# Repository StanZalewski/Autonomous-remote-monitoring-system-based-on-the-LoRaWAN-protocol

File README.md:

# Autonomous Remote Monitoring System (LoRaWAN)

Solar-powered agricultural weather station built from scratch: three custom PCBs, three MCUs, Modbus RTU over RS-485 between boards, LoRaWAN uplink to a private ChirpStack network server. Verified 4.3 km link in suburban terrain.

Bachelor's thesis project, Poznan University of Technology, 2026.

---

## What it does

A field station measures temperature, humidity, pressure and ambient light, runs entirely off a 30 W solar panel with a 3S LiFePO4 pack, and reports over LoRaWAN to a self-hosted network server. No GSM, no mains power, no cloud dependency.

| | |
|---|---|
| **Boards designed** | 3 (two 4-layer, one 2-layer), schematic → routing → assembly → bring-up |
| **Bare-metal drivers written** | 5, from IC datasheets: BMP390, SHT45, VEML7700, BQ25798, BQ76952 |
| **Verified LoRa range** | 4.3 km, suburban terrain, low-mounted gateway |
| **Inter-board protocol** | Modbus RTU over RS-485, master–slave, expandable to 32 nodes |
| **MCUs** | STM32WLE5CC (RAK3172 master), 2× STM32G030F6 (slaves) |

---

## System architecture

```mermaid
flowchart LR
  ED["End device<br/>3 PCBs, Modbus RTU"] -->|"LoRa 868 MHz"| GW["RAK5146 gateway<br/>ChirpStack Gateway OS"]
  GW -->|Ethernet| LNS["ChirpStack v4<br/>network server"]
  LNS -->|MQTT| BR["Mosquitto broker"]
  BR --> DB[("InfluxDB<br/>time-series")]
  BR --> WEB["Web interface"]
  DB --> WEB
```

### End device

```mermaid
flowchart TB
  M["<b>Master</b><br/>RAK3172 (STM32WLE5CC)<br/>LoRaWAN + GPS"]
  P["<b>Power board</b><br/>BQ25798 MPPT charger<br/>BQ76952 BMS<br/>STM32G030F6"]
  S["<b>Sensor board</b><br/>SHT45 · BMP390 · VEML7700<br/>STM32G030F6"]
  M ---|"RS-485 bus"| P
  M ---|"RS-485 bus"| S
```

The split into three boards is deliberate: each module is reusable on its own, and new slaves can be added to the bus without touching the existing hardware.

---

## Hardware

### Wireless transceiver — master (4-layer)

RAK3172 (STM32WLE5CC) running the LoRaWAN stack and mastering the Modbus bus, plus a Quectel LC76GABMD GNSS receiver. USB-C to UART via FT234XD behind an STISO621 optoisolator for bench work, SP3485EN for the RS-485 side, TLV75533 LDO.

| Top | Bottom | Assembled |
|---|---|---|
|  |  |  |

Both antennas are fed by 50 Ω controlled-impedance traces — 0.3493 mm width computed for the JLCPCB FR-4 stackup, with a pi network at each antenna for fine tuning. The GNSS feed runs up the centre of the board inside a via fence, with the SMD antenna (E1) at the top edge and the whole area kept clear of copper on the layer below. The RAK3172 sits in the opposite corner with its own SMA feed, so the two RF chains never share a return path. Power electronics and high-current traces are pushed as far from both as the outline allows.

Schematics: [RAK3172 and peripherals](docs/schematics/transceiver-rak3172.svg) · [GNSS section](docs/schematics/transceiver-gps.svg)

### Power electronics — slave (4-layer)

BQ25798 buck-boost charger with MPPT harvesting from a 30 W panel into a 3S LiFePO4 pack, BQ76952 BMS, STM32G030F6 supervising both over a galvanically isolated I²C bus.

| Top | Bottom | Assembled |
|---|---|---|
|  |  |  |

Two constraints drove this layout: minimise EMI, minimise high-current path length. The 2.2 µH inductor sits at the top (750 kHz switching was chosen over the 1 µH / 1.5 MHz option for better efficiency and lower EMI), decoupling caps are pulled tight to the charger's VBUS, SYS, PMID and BAT pins, and the analog and power grounds are split and joined at a single point between C10 and C11. The BMS and its circuitry are placed physically between the MCU and the charger as a buffer against the switching node. The charge and discharge FETs sit top-right of the BMS to keep pack current paths short, and the 1 mΩ shunt (R23) divides BMS ground from system ground. Everything crossing to the MCU passes through ISO1640 (I²C) and Si8662 (ALERT, INT, CE) isolators, fed by isolated 5 V and 12 V DC-DC bricks.

Schematics: [BQ25798 charger](docs/schematics/power-charger-bq25798.svg) · [BQ76952 BMS](docs/schematics/power-bms-bq76952.svg) · [MCU and isolation](docs/schematics/power-mcu-g030f6.svg)

### Data gathering — slave (2-layer)

SHT45 (±0.1 °C, ±1 %RH), BMP390 (±0.33 hPa) and VEML7700 on one I²C bus, read by an STM32G030F6 and exposed as Modbus registers. Spare GPIO is broken out to terminal blocks for wind and rain sensors.

| Top | Bottom | Assembled |
|---|---|---|
|  |  |  |

The VEML7700 is mounted alone on the back face; everything else lives on the front. That keeps direct sun off the SHT45, which would otherwise bias the temperature reading, and leaves the light sensor as the only protrusion on its side so the enclosure aperture can stay small. The bottom face is a solid ground pour for a continuous low-impedance return, and the LDO sits next to the terminal blocks to keep the long, EMI-prone wiring runs away from the sensor traces.

Schematic: [sensor board](docs/schematics/sensor-board.svg)

---

## Firmware

Written bare-metal against the datasheets on a CMake / `arm-none-eabi` toolchain, not inside an IDE. Each module follows the same three-way split:

```
<Module>/
├── App/          # init, control, RS-485 dock — application logic
├── Core/         # CubeMX-generated, with calls into App/
├── Drivers_IC/   # or Drivers_Sensors/ — direct IC control
└── Drivers_ModbusRTU/
```

Keeping everything outside `Core/` means CubeMX regeneration never touches hand-written code, and the drivers port to another MCU without untangling them first.

### Power module sequence

```mermaid
flowchart TB
  A["fullInitialization()<br/>health check → configure → verify<br/>→ open CHG/DSG FETs → enable charging"]
  B["RS485_Init()<br/>RE/DE low, UART RX interrupt"]
  C["GenSysInfo()<br/>cell voltages, pack temps, FET state"]
  D["RS485_UpdateRegisters()"]
  E["RS485_Process()<br/>handle master requests"]
  F["every 60 s:<br/>WatchDogs_R() → HealthCheck() → UpdateFlags()"]
  A --> B --> C --> D --> E --> C
  E -.-> F
  F -.-> C
```

The board only comes up if the charger's VBUS is live: with the BMS FETs open, the isolated side has no power and I²C would fail, so the charger's default battery profile bootstraps the DC-DC that feeds the MCU. Initialisation then health-checks both ICs (device ID on the bus, no fault flags raised), configures them, verifies the critical registers read back correctly, and only then opens the CHG and DSG FETs so the charger sees the pack on its BAT pin.

Both ICs run hardware watchdogs with an 80 s timeout; the loop kicks them every 60 s and re-runs the same health check used at boot. Fault and status registers are mirrored into Modbus registers, so a fault on the power board propagates to the master and out over LoRa rather than silently bricking the station.

### LoRa payload

Uplinks are packed hexadecimal, not JSON — air time matters under the EU 1% duty cycle. Each payload opens with a two-byte identifier (payload class + device ID matching the Modbus address). Values are sent unscaled big-endian `uint16_t`, with signed quantities cast from `int16_t`; pressure and lux use `uint32_t`. Example: a cell voltage of 3.456 V goes out as `3456` → `0x0D80`.

| Payload ID | Contents |
|---|---|
| `0x01` | Cell voltages 1–3, pack temperature (BMS side, charger side) |
| `0x11` | VAC_1 voltage, system info, BMS current |
| `0x21`–`0x81` | Fault checks, fault flags, charger flags, BMS safety alerts/status, PF alert/status |
| `0x02` | SHT45 temperature, SHT45 humidity, BMP390 temperature |
| `0x12` | VEML7700 lux, white ratio, BMP390 pressure |

Because sensor data is split across payload classes, the decoder keeps a per-station cache and merges partial updates into a complete record.

---

## Network side

A private LoRaWAN deployment rather than The Things Network — too few public gateways in the test area, and no control over their uptime. ChirpStack v4 runs in Docker Compose on an Odroid H4; the gateway is a Raspberry Pi with a RAK5146 concentrator HAT running ChirpStack Gateway OS, feeding an 80 cm outdoor fiberglass omni.

---

## Results and what didn't work

Worth reading before the achievements list. Three limitations showed up only in the field:

**DC-DC efficiency at low load.** The converter draws more quiescent current than budgeted, so after roughly 10 hours without sun the station drops out and stays down until the panel recovers. Fine for summer, not good enough for a Polish winter. A lower-Iq regulator and a proper sleep state for the master are the fix.

**LiFePO4 below freezing.** The cells cannot be charged below 0 °C without permanent damage, and this wasn't caught at design time. Sub-zero temperatures are normal here in winter, so a heater circuit and a charge inhibit tied to the BMS thermistor are required for year-round autonomy.

**GPS never acquires a fix.** The LC76GABMD powers up and outputs data over UART, but no satellites are found even after 30 minutes with a clear sky view. Most likely the passive SMD antenna placement and matching — the next revision needs the ground-plane keepout and feed geometry reworked against the Quectel application note, and an active antenna as a fallback.

What did work: Modbus RTU between modules ran without a single bus fault across deployment, the LoRaWAN join succeeded at 4.3 km despite a gateway mounted low with terrain intruding into the Fresnel zone, and the charger/BMS pair managed the solar-to-battery handover autonomously.

---

## In progress: anemometer

The sensor board breaks out spare GPIO to terminal blocks specifically so wind and rain sensors can be added without a redesign. The anemometer is the first of them — mechanically designed, board routed, not yet built.

| Cross-section | Sensor PCB |
|---|---|
|  |  |

Three-cup rotor on a vertical shaft running in two stacked bearings, with the rotating magnet passing directly over a Hall sensor on a round PCB at the base of the housing. The board is the smallest one in the project: a 5 V to 3.3 V regulator (U3) with its decoupling, the Hall sensor (U1), a pull-up on its open-drain output (R1), and three pads — 5 V, GND, OUT. Output is a pulse train straight into one of the sensor board's binary inputs, so wind speed becomes a frequency count rather than another I²C device on the bus.

The board outline wraps the shaft bore, and the signal trace is routed the long way around the perimeter rather than across the centre, keeping it clear of the bore and the mounting holes. The housing overhangs the whole assembly so the bearings and electronics sit under a drip edge.

Not yet fabricated — the mechanical design is done, the electrical design is done, and the build was cut for time.

---

## Build

```bash
cmake -B build -DCMAKE_TOOLCHAIN_FILE=cmake/arm-none-eabi.cmake
cmake --build build
```

Flash with `st-flash` or an ST-Link through OpenOCD. The RAK3172 is configured through RUI3 APIs; the two STM32G030F6 slaves are flashed over SWD on the KAmod BlackPico headers.

---

## Repository layout

```
PowerManagementModule/     # STM32G030F6 — charger, BMS, Modbus slave
DataGatheringModule/       # STM32G030F6 — sensors, Modbus slave
TransceiverModule/         # RAK3172 — Modbus master, LoRaWAN uplink
hardware/                  # KiCad projects, Gerbers, BOMs
docs/img/                  # board renders and photos
docs/schematics/           # exported schematic sheets
```

---

## Authorship

Joint bachelor's thesis with **Jakub Wesołowski**, supervised by dr inż. Bartłomiej Wicher.

This repository covers the end device. My contribution: hardware design and PCB layout of all three boards, all embedded firmware and IC drivers, the Modbus RTU / RS-485 transport, the LoRa payload protocol, and the end-device integration with the ChirpStack network server (thesis sections 2 and 3.2–3.6).

The application layer — MQTT broker, InfluxDB schema, web interface and the Gradient Boosting prediction model (sections 3.1, 3.7 and chapter 4) — is Jakub's work.

---

## License

MIT for the firmware. Hardware files under CERN-OHL-P v2.

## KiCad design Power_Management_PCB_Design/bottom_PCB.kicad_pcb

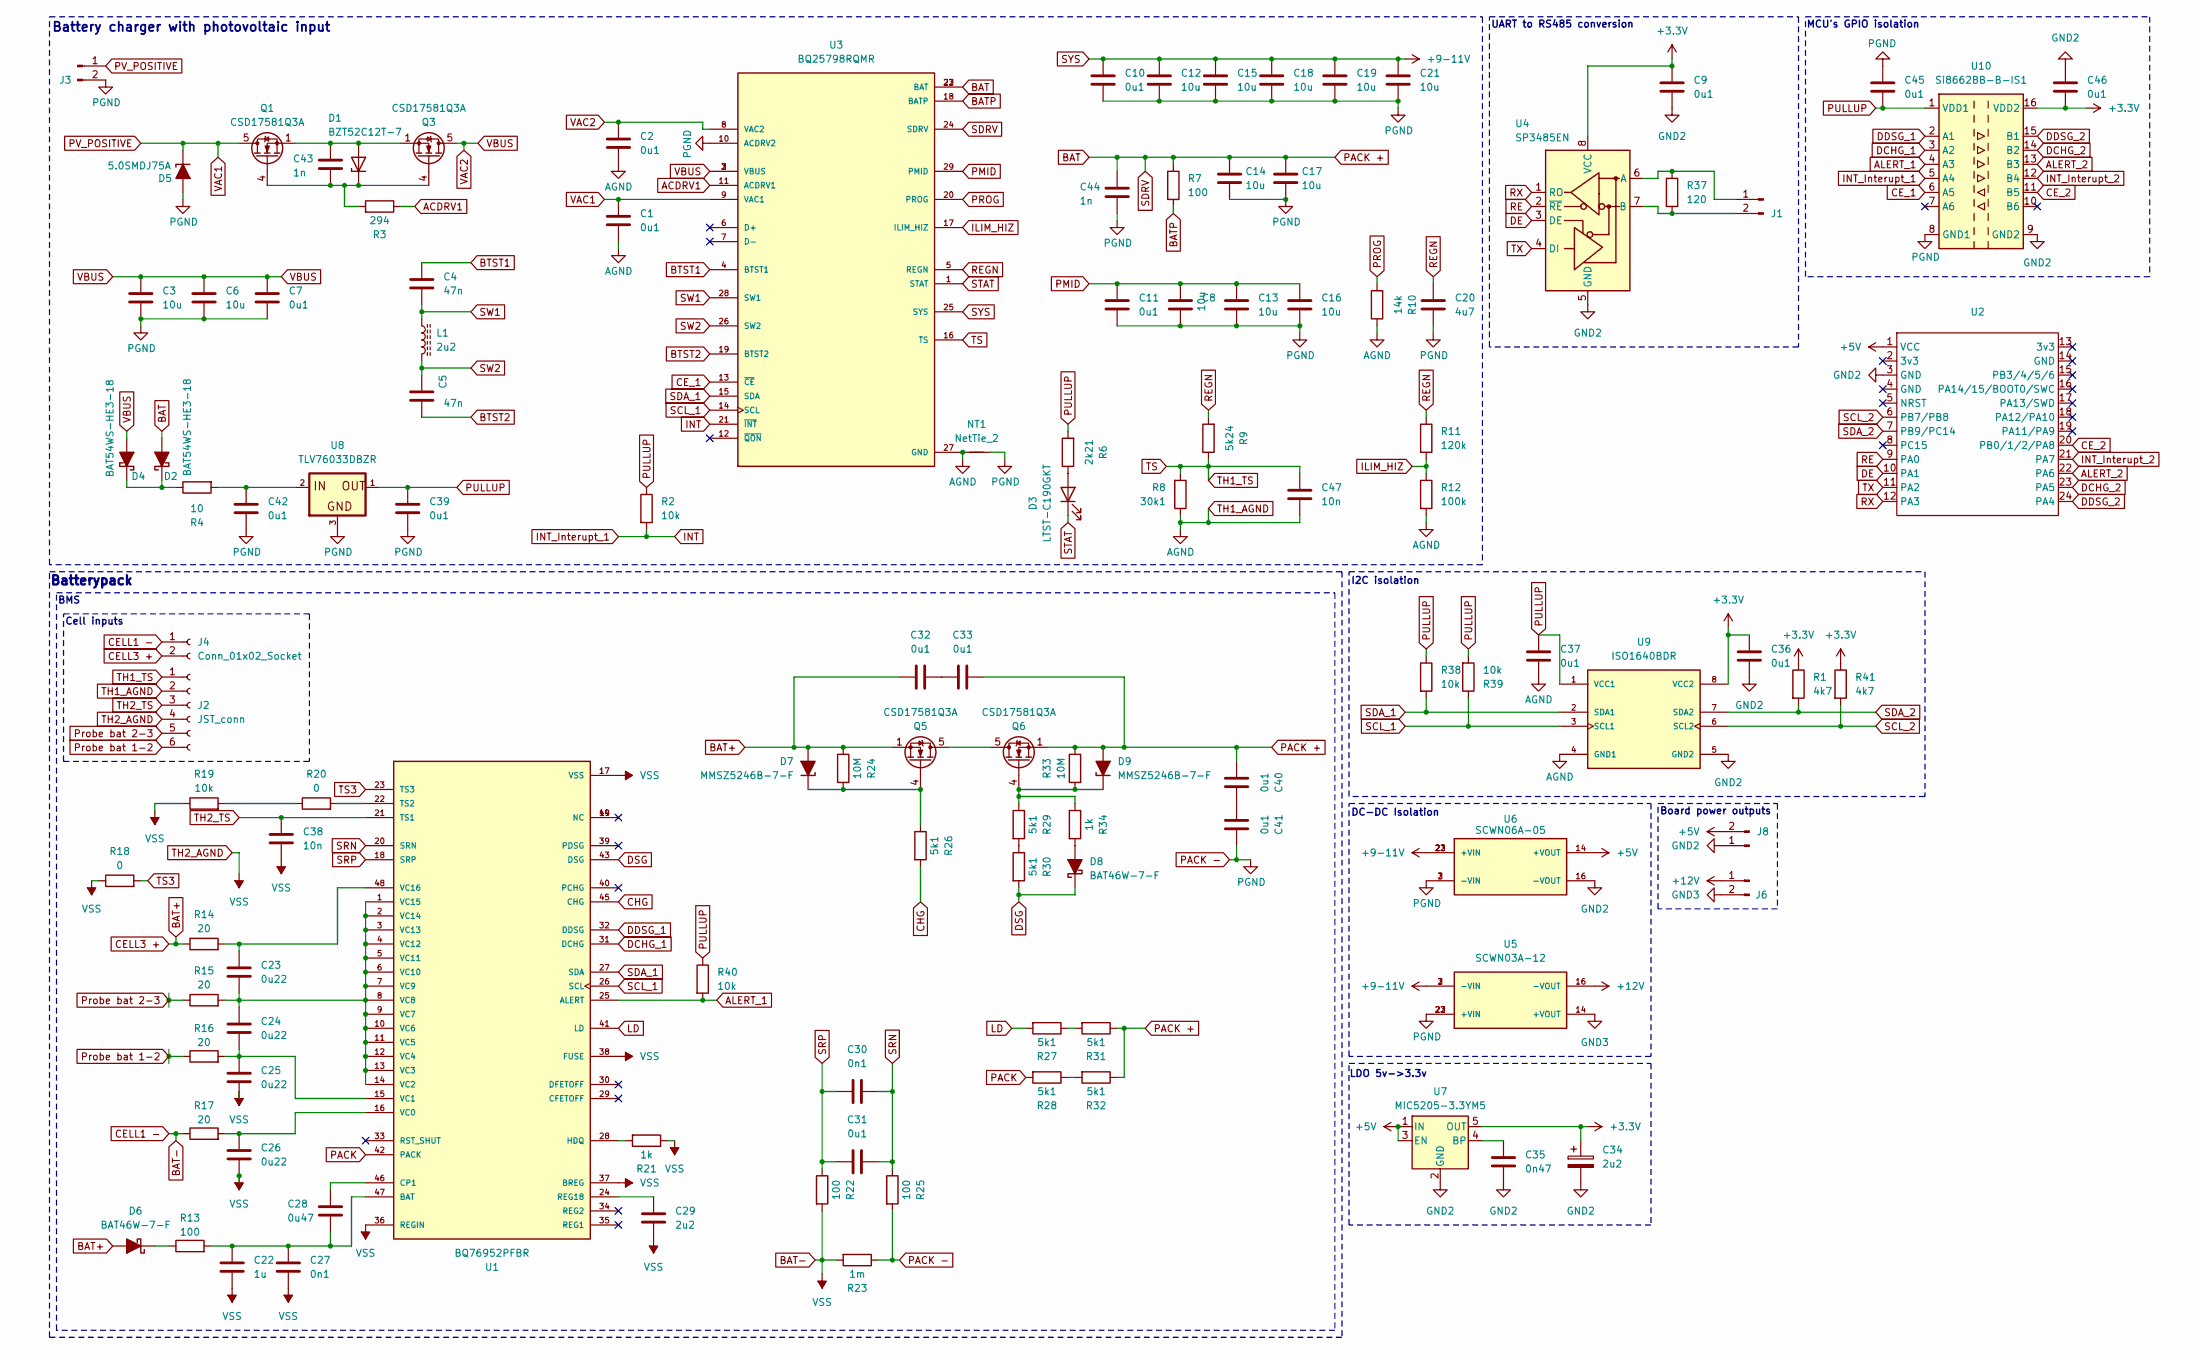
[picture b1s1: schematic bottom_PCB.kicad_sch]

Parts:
C1, C2, C7, C9, C10, C11, C31, C32, C33, C36, C37, C39, C40, C41, C42, C45, C46: 0u1; C_0603_1608Metric_Pad1.08x0.95mm_HandSolder
C3, C6, C8, C12, C13, C15, C16, C18, C19, C21: 10u; C_1206_3216Metric_Pad1.33x1.80mm_HandSolder
C4, C5: 47n; C_0603_1608Metric_Pad1.08x0.95mm_HandSolder
C14, C17: 10u; C_0603_1608Metric_Pad1.08x0.95mm_HandSolder
C20: 4u7; C_0603_1608Metric_Pad1.08x0.95mm_HandSolder
C22: 1u; C_1206_3216Metric_Pad1.33x1.80mm_HandSolder
C23, C24, C25, C26: 0u22; C_0603_1608Metric_Pad1.08x0.95mm_HandSolder
C27, C30: 0n1; C_0603_1608Metric_Pad1.08x0.95mm_HandSolder
C28: 0u47; C_0805_2012Metric_Pad1.18x1.45mm_HandSolder
C29: 2u2; C_0805_2012Metric_Pad1.18x1.45mm_HandSolder
C34: 2u2; C_1206_3216Metric_Pad1.33x1.80mm_HandSolder
C35: 0n47; C_0603_1608Metric_Pad1.08x0.95mm_HandSolder
C38, C47: 10n; C_0805_2012Metric_Pad1.18x1.45mm_HandSolder
C43, C44: 1n; C_0603_1608Metric_Pad1.08x0.95mm_HandSolder
D1: BZT52C12T-7; D_SOD-523
D2, D4: BAT54WS-HE3-18; D_SOD-323_HandSoldering
D3: LTST-C190GKT; LED_0603_1608Metric_Pad1.05x0.95mm_HandSolder
D5: 5.0SMDJ75A; DIOM6859X262N
D6, D8: BAT46W-7-F; D_SOD-123
D7, D9: MMSZ5246B-7-F; D_SOD-123
J1, J6, J8: Conn_01x02_Pin; SPTAF 1_2-3,5-IL
J2: JST_conn; JST_PH_B6B-PH-K_1x06_P2.00mm_Vertical
J3: Conn_01x02_Pin; conn_SMD_wire_2x1_Power
J4: Conn_01x02_Socket; AMASS_XT60-M_1x02_P7.20mm_Vertical
L1: 2u2; SPM6530T-2R2M
NT1: NetTie_2; NetTie
Q1, Q3, Q5, Q6: CSD17581Q3A; VSON-8_3.3x3.3mm_P0.65mm_NexFET
R1, R41: 4k7; R_0603_1608Metric_Pad0.98x0.95mm_HandSolder
R2, R38, R39, R40: 10k; R_0603_1608Metric_Pad0.98x0.95mm_HandSolder
R3: 294; R_0603_1608Metric_Pad0.98x0.95mm_HandSolder
R4: 10; R_1206_3216Metric_Pad1.30x1.75mm_HandSolder
R6: 2k21; R_0603_1608Metric_Pad0.98x0.95mm_HandSolder
R7, R13, R22, R25: 100; R_0603_1608Metric_Pad0.98x0.95mm_HandSolder
R8: 30k1; R_0603_1608Metric_Pad0.98x0.95mm_HandSolder
R9: 5k24; R_0603_1608Metric_Pad0.98x0.95mm_HandSolder
R10: 14k; R_0603_1608Metric_Pad0.98x0.95mm_HandSolder
R11: 120k; R_0603_1608Metric_Pad0.98x0.95mm_HandSolder
R12: 100k; R_0603_1608Metric_Pad0.98x0.95mm_HandSolder
R14, R15, R16, R17: 20; R_0805_2012Metric_Pad1.20x1.40mm_HandSolder
R18, R20: 0; R_0603_1608Metric_Pad0.98x0.95mm_HandSolder
R19: 10k; R_1206_3216Metric_Pad1.30x1.75mm_HandSolder
R21: 1k; R_0603_1608Metric
R23: 1m; R_1210_3225Metric_Pad1.30x2.65mm_HandSolder
R24, R33: 10M; R_0603_1608Metric_Pad0.98x0.95mm_HandSolder
R26, R27, R28, R29, R30, R31, R32: 5k1; R_0805_2012Metric_Pad1.20x1.40mm_HandSolder
R34: 1k; R_0805_2012Metric_Pad1.20x1.40mm_HandSolder
R37: 120; R_0603_1608Metric_Pad0.98x0.95mm_HandSolder
U1: BQ76952PFBR; TQFP-48_7x7mm_P0.5mm; PARTREV B
U2: STM32G030
U3: BQ25798RQMR; IC_BQ25798RQMR; PARTREV B
U4: SP3485EN; SOIC-8_3.9x4.9mm_P1.27mm
U5: SCWN03A-12; DIP1524W50P254L3180H1020Q8B; PARTREV N/A
U6: SCWN06A-05; DIP1524W50P254L3180H1020Q8B; PARTREV N/A
U7: MIC5205-3.3YM5; SOT-23-5
U8: TLV76033DBZR; SOT-23-3
U9: ISO1640BDR; SOIC127P599X175-8N; PARTREV D
U10: Si8662BB-B-IS1; SOIC-16_3.9x9.9mm_P1.27mm

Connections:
+3.3V: C9.1, C34.1, C36.1, C46.2, R1.1, R41.1, U4.8 (VCC), U7.5 (OUT), U9.8 (VCC2), U10.16 (VDD2)
+5V: J8.2, U2.1 (VCC), U6.14 (+VOUT), U7.1 (IN), U7.3 (EN)
+12V: J6.1, U5.16 (-VOUT)
ACDRV1: R3.1, U3.11 (ACDRV1)
ALERT_1: R40.2, U1.25 (ALERT), U10.4 (A3)
ALERT_2: U2.22 (PA6), U10.13 (B3)
BAT: C14.1, C17.1, C33.2, C40.1, C44.1, D2.2 (A), D9.2 (A), Q6.1 (S), Q6.2 (S), Q6.3 (S), R7.1, R31.1, R32.1, R33.1, U3.22 (BAT), U3.23 (BAT), U3.24 (SDRV)
BAT+: C32.1, D6.2 (A), D7.2 (A), J4.2, Q5.1 (S), Q5.2 (S), Q5.3 (S), R14.1, R24.1
BAT-: C22.2, C25.2, C26.2, C27.2, C29.2, C38.2, J2.4, J4.1, R17.1, R18.1, R19.1, R21.1, R22.2, R23.2, U1.17 (VSS), U1.36 (REGIN), U1.37 (BREG), U1.38 (FUSE)
BATP: R7.2, U3.18 (BATP)
BTST1: C4.1, U3.4 (BTST1)
BTST2: C5.2, U3.19 (BTST2)
CE_1: U3.13 (~CE), U10.6 (A5)
CE_2: U2.20 (PB0/1/2/PA8), U10.11 (B5)
CHG: R26.2, U1.45 (CHG)
DCHG_1: U1.31 (DCHG), U10.3 (A2)
DCHG_2: U2.23 (PA5), U10.14 (B2)
DDSG_1: U1.32 (DDSG), U10.2 (A1)
DDSG_2: U2.24 (PA4), U10.15 (B1)
DE: U2.10 (PA1), U4.3 (DE)
DSG: D8.1 (K), R30.2, U1.43 (DSG)
GND2: C9.2, C34.2, C35.2, C36.2, C46.1, J8.1, U2.3 (GND), U4.5 (GND), U6.16 (-VOUT), U7.2 (GND), U9.5 (GND2), U10.9 (GND2)
GND3: J6.2, U5.14 (+VOUT)
ILIM_HIZ: R11.2, R12.1, U3.17 (ILIM_HIZ)
INT: R2.2, U3.21 (~INT), U10.5 (A4)
INT_Interupt_2: U2.21 (PA7), U10.12 (B4)
LD: R27.2, U1.41 (LD)
unnamed: C32.2, C33.1
unnamed: C40.2, C41.1
unnamed: C42.1, R4.2, U8.2
unnamed: C43.1, D1.2 (A), Q1.1 (S), Q1.2 (S), Q1.3 (S), Q3.1 (S), Q3.2 (S), Q3.3 (S)
unnamed: C43.2, D1.1 (K), Q1.4 (G), Q3.4 (G), R3.2
unnamed: D2.1 (K), D4.1 (K), R4.1
unnamed: D3.2 (A), R6.1
unnamed: D6.1 (K), R13.1
unnamed: D7.1 (K), Q5.4 (G), R24.2, R26.1
unnamed: D8.2 (A), R34.2
unnamed: D9.1 (K), Q6.4 (G), R29.1, R33.2, R34.1
unnamed: J1.1, R37.1, U4.6 (A)
unnamed: J1.2, R37.2, U4.7 (B)
unnamed: Q5.5 (D), Q6.5 (D)
unnamed: R19.2, R20.1
unnamed: R27.1, R31.2
unnamed: R28.1, R32.2
unnamed: R29.2, R30.1
unnamed: C22.1, C27.1, C28.2, R13.2, U1.47 (BAT)
unnamed: C28.1, U1.46 (CP1)
unnamed: R21.2, U1.28 (HDQ)
unnamed: C29.1, U1.24 (REG18)
unnamed: R20.2, U1.22 (TS2)
unnamed: C26.1, R17.2, U1.16 (VC0)
unnamed: C24.2, C25.1, R16.2, U1.15 (VC1)
unnamed: C23.2, C24.1, R15.2, U1.1 (VC15), U1.2 (VC14), U1.3 (VC13), U1.4 (VC12), U1.5 (VC11), U1.6 (VC10), U1.7 (VC9), U1.8 (VC8), U1.9 (VC7), U1.10 (VC6), U1.11 (VC5), U1.12 (VC4), U1.13 (VC3), U1.14 (VC2)
unnamed: C23.1, R14.2, U1.48 (VC16)
unnamed: C35.1, U7.4 (BP)
PACK: R28.2, U1.42 (PACK)
PACK -: C3.2, C6.2, C7.2, C8.2, C10.2, C11.2, C12.2, C13.2, C14.2, C15.2, C16.2, C17.2, C18.2, C19.2, C20.2, C21.2, C39.2, C41.2, C42.2, C44.2, C45.1, D5.2 (A), J3.2, NT1.2, R23.1, R25.2, U3.10 (ACDRV2), U5.22 (+VIN), U5.23 (+VIN), U6.2 (-VIN), U6.3 (-VIN), U8.3, U10.8 (GND1)
PMID: C8.1, C11.1, C13.1, C16.1, U3.29 (PMID)
PROG: R10.2, U3.20 (PROG)
PULLUP: C37.1, C39.1, C45.2, R2.1, R6.2, R38.1, R39.2, R40.1, U8.1, U9.1 (VCC1), U10.1 (VDD1)
PV_POSITIVE: C1.1, D5.1 (K), J3.1, Q1.5 (D), U3.9 (VAC1)
Probe bat 1-2: J2.6, R16.1
Probe bat 2-3: J2.5, R15.1
RE: U2.9 (PA0), U4.2 (~RE)
REGN: C20.1, R9.2, R11.1, U3.5 (REGN)
RX: U2.12 (PA3), U4.1 (RO)
SCL_1: R39.1, U1.26 (SCL), U3.14 (SCL), U9.3 (SCL1)
SCL_2: R41.2, U2.6 (PB7/PB8), U9.6 (SCL2)
SDA_1: R38.2, U1.27 (SDA), U3.15 (SDA), U9.2 (SDA1)
SDA_2: R1.2, U2.7 (PB9/PC14), U9.7 (SDA2)
SRN: C30.2, C31.2, R25.1, U1.20 (SRN)
SRP: C30.1, C31.1, R22.1, U1.18 (SRP)
STAT: D3.1 (K), U3.1 (STAT)
SW1: C4.2, L1.1, U3.28 (SW1)
SW2: C5.1, L1.2, U3.26 (SW2)
SYS: C10.1, C12.1, C15.1, C18.1, C19.1, C21.1, U3.25 (SYS), U5.2 (-VIN), U5.3 (-VIN), U6.22 (+VIN), U6.23 (+VIN)
TH1_AGND: C1.2, C2.2, C37.2, C47.2, J2.2, NT1.1, R8.1, R10.1, R12.2, U3.27 (GND), U9.4 (GND1)
TH1_TS: C47.1, J2.1, R8.2, R9.1, U3.16 (TS)
TH2_TS: C38.1, J2.3, U1.21 (TS1)
TS3: R18.2, U1.23 (TS3)
TX: U2.11 (PA2), U4.4 (DI)
VAC2: C2.1, C3.1, C6.1, C7.1, D4.2 (A), Q3.5 (D), U3.2 (VBUS), U3.3 (VBUS), U3.8 (VAC2)

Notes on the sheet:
LDO 5v->3.3v
UART to RS485 conversion
Cell inputs
MCU's GPIO isolation
Board power outputs
I2C isolation
BMS
Battery charger with photovoltaic input
Batterypack
DC-DC Isolation

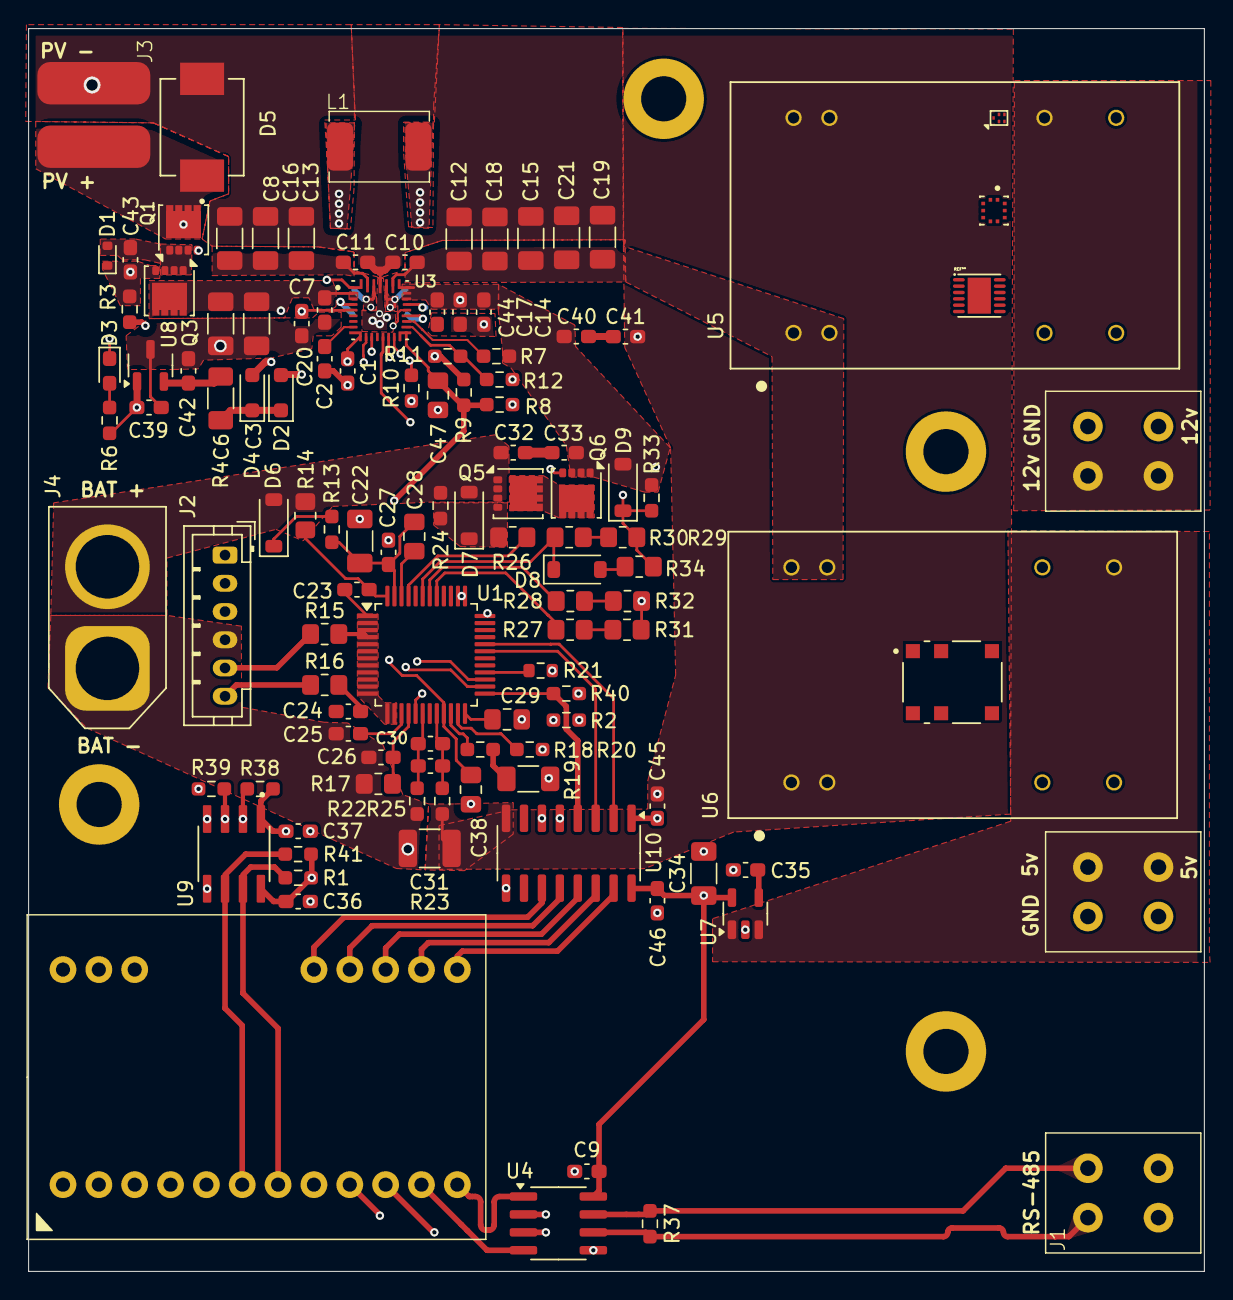
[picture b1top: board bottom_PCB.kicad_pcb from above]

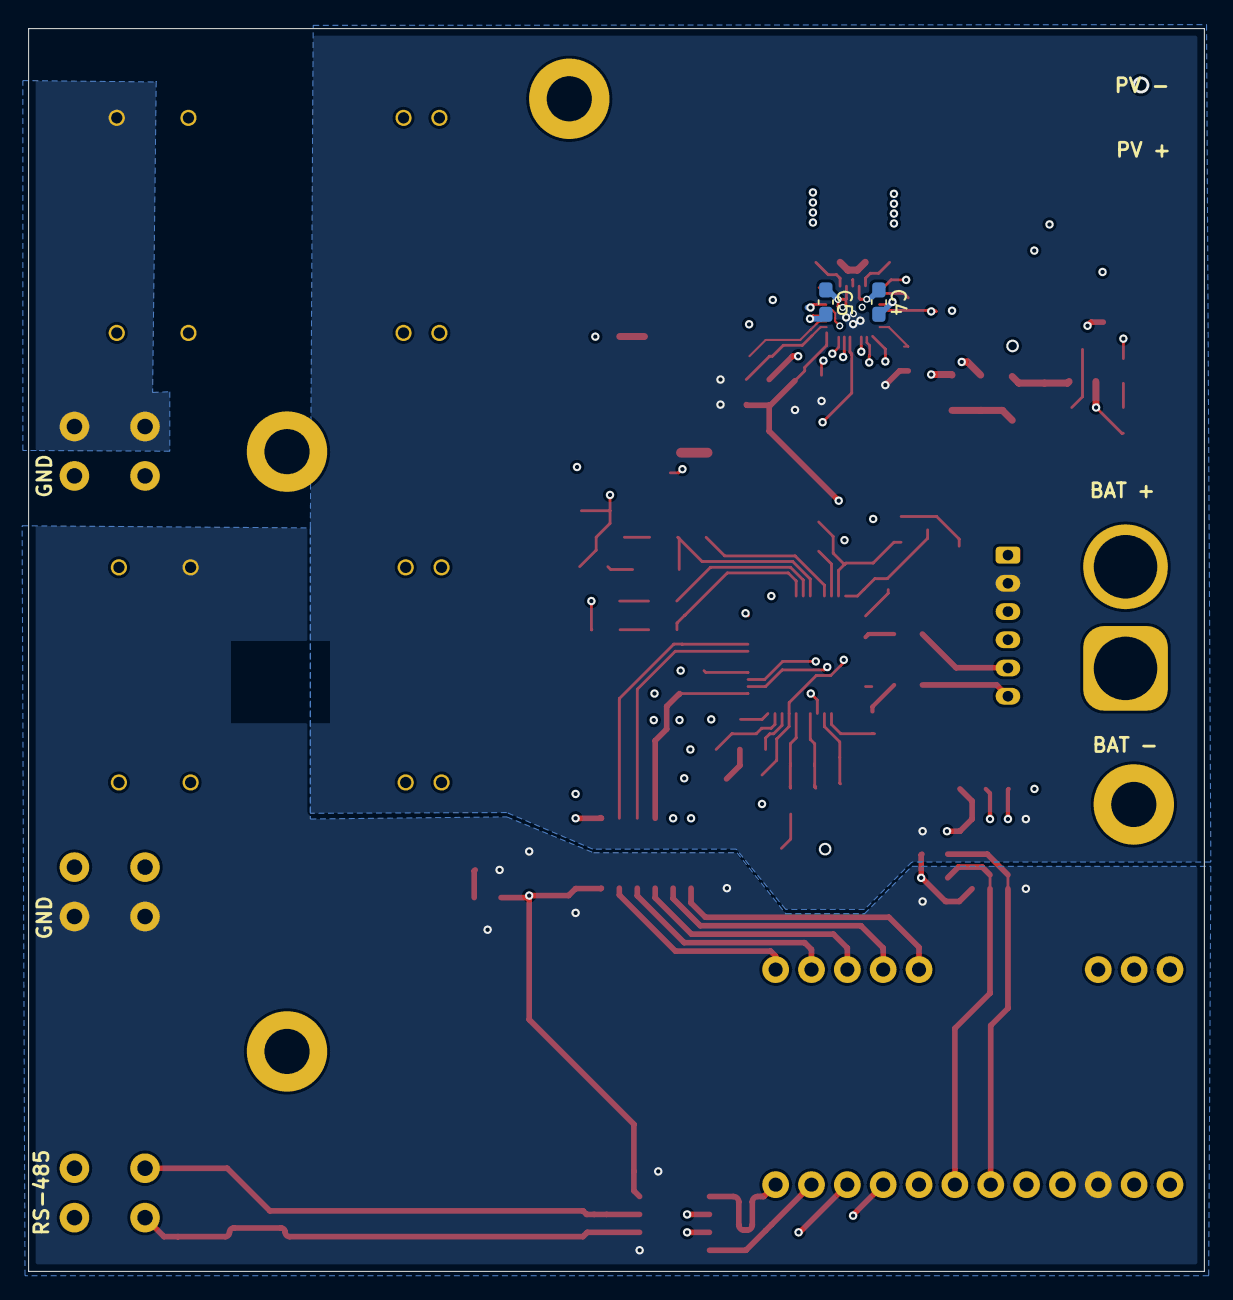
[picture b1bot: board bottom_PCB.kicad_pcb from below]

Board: 4 copper layers, 83.3 x 88.1 mm, 116 parts (2 on the bottom side), 82 nets.

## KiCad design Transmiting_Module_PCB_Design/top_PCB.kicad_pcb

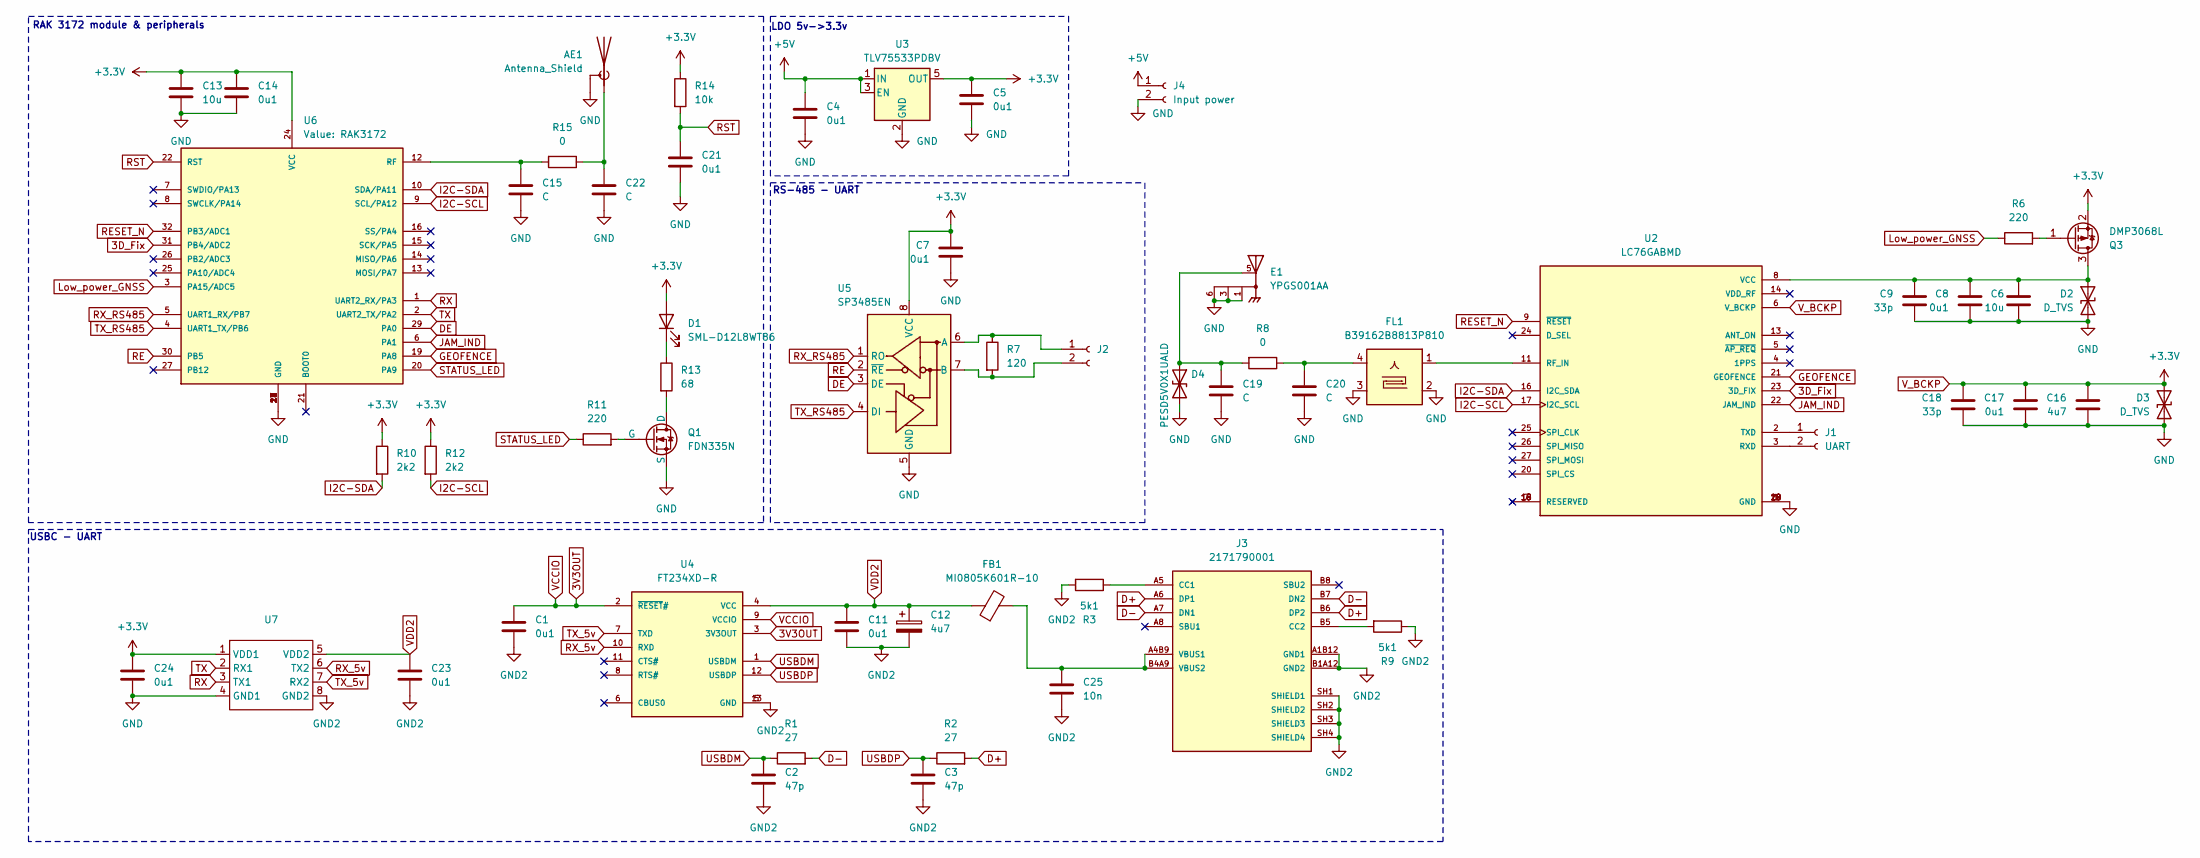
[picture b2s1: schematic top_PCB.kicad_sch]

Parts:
AE1: Antenna_Shield; SMA_Molex_73251-1153_EdgeMount_Horizontal
C1, C4, C5, C7, C8, C11, C14, C17, C21, C23, C24: 0u1; C_0603_1608Metric_Pad1.08x0.95mm_HandSolder
C2, C3: 47p; C_0603_1608Metric_Pad1.08x0.95mm_HandSolder
C6, C13: 10u; C_1206_3216Metric_Pad1.33x1.80mm_HandSolder
C9, C18: 33p; C_0603_1608Metric_Pad1.08x0.95mm_HandSolder
C12: 4u7; C_1206_3216Metric_Pad1.33x1.80mm_HandSolder
C15, C19, C20, C22: C; C_0603_1608Metric_Pad1.08x0.95mm_HandSolder
C16: 4u7; C_0603_1608Metric_Pad1.08x0.95mm_HandSolder
C25: 10n; C_0603_1608Metric_Pad1.08x0.95mm_HandSolder
D1: SML-D12L8WT86; LED_0603_1608Metric_Pad1.05x0.95mm_HandSolder
D2, D3: D_TVS; Nexperia_DSN0603-2_0.6x0.3mm_P0.4mm
D4: PESD5V0X1UALD; D_SOD-882D
E1: YPGS001AA; XDCR_YPGS001AA; PARTREV 2.2mm
FB1: MI0805K601R-10; R_0805_2012Metric_Pad1.20x1.40mm_HandSolder
FL1: B39162B8813P810; Filter_1109-5_1.1x0.9mm
J1: UART; JST_PH_B2B-PH-K_1x02_P2.00mm_Vertical
J2: Conn_01x02_Socket; SPTAF 1_2-3,5-IL
J3: 2171790001; MOLEX_2171790001; PARTREV A1
J4: Input power; SPTAF 1_2-3,5-IL
Q1: FDN335N; SOT-23-FDN335N
Q3: DMP3068L; SOT-23
R1, R2: 27; R_0603_1608Metric_Pad0.98x0.95mm_HandSolder
R3, R9: 5k1; R_0805_2012Metric_Pad1.20x1.40mm_HandSolder
R6, R11: 220; R_0805_2012Metric_Pad1.20x1.40mm_HandSolder
R7: 120; R_0603_1608Metric_Pad0.98x0.95mm_HandSolder
R8, R15: 0; R_0402_1005Metric_Pad0.72x0.64mm_HandSolder
R10, R12: 2k2; R_0603_1608Metric_Pad0.98x0.95mm_HandSolder
R13: 68; R_1206_3216Metric_Pad1.30x1.75mm_HandSolder
R14: 10k; R_0603_1608Metric_Pad0.98x0.95mm_HandSolder
U2: LC76GABMD; PARTREV 1.0
U3: TLV75533PDBV; SOT-23-5
U4: FT234XD-R; SON45P300X300X80-13N; PARTREV Version 1.2
U5: SP3485EN; SOIC-8_3.9x4.9mm_P1.27mm
U6: RAK3172
U7: SO8N

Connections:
3D_Fix: U2.23 (3D_FIX), U6.31 (PB4/ADC2)
3V3OUT: C1.1, U4.2 (~RESET#), U4.3 (3V3OUT), U4.9 (VCCIO)
+5V: C4.1, J4.1, U3.1 (IN), U3.3 (EN)
D+: J3.A6 (DP1), J3.B6 (DP2), R2.2
D-: J3.A7 (DN1), J3.B7 (DN2), R1.2
DE: U5.3 (DE), U6.29 (PA0)
GEOFENCE: U2.21 (GEOFENCE), U6.19 (PA8)
GND: AE1.2 (Shield), C4.2, C5.2, C6.2, C7.2, C8.2, C9.2, C13.2, C14.2, C15.2, C16.2, C17.2, C18.2, C19.2, C20.2, C21.2, C22.2, C24.2, D2.2 (A2), D3.2 (A2), D4.2 (A2), E1.1, E1.3, E1.6, FL1.2, FL1.3, FL1.5, J4.2, Q1.3 (S), U2.1 (GND), U2.10 (GND), U2.12 (GND), U2.28 (GND), U3.2 (GND), U5.5 (GND), U6.11 (GND), U6.17 (GND), U6.18 (GND), U6.23 (GND), U6.28 (GND), U7.4 (GND1)
GND2: C1.2, C2.2, C3.2, C11.2, C12.2, C23.2, C25.2, J3.A1B12 (GND1), J3.B1A12 (GND2), J3.SH1 (SHIELD1), J3.SH2 (SHIELD2), J3.SH3 (SHIELD3), J3.SH4 (SHIELD4), R3.2, R9.1, U4.5 (GND), U4.13 (GND), U7.8 (GND2)
I2C-SCL: R12.2, U2.17 (I2C_SCL), U6.9 (SCL/PA12)
I2C-SDA: R10.2, U2.16 (I2C_SDA), U6.10 (SDA/PA11)
JAM_IND: U2.22 (JAM_IND), U6.6 (PA1)
Low_power_GNSS: R6.1, U6.3 (PA15/ADC5)
unnamed: AE1.1 (A), C22.1, R15.1
unnamed: C20.1, FL1.4, R8.1
unnamed: D1.1 (K), R13.1
unnamed: C6.1, C8.1, C9.1, D2.1 (A1), Q3.3 (D), U2.8 (VCC)
unnamed: C19.1, D4.1 (A1), E1.5, R8.2
unnamed: J1.1, U2.2 (TXD)
unnamed: J1.2, U2.3 (RXD)
unnamed: J2.1, R7.1, U5.6 (A)
unnamed: J2.2, R7.2, U5.7 (B)
unnamed: J3.A5 (CC1), R3.1
unnamed: J3.B5 (CC2), R9.2
unnamed: C25.1, FB1.2, J3.A4B9 (VBUS1), J3.B4A9 (VBUS2)
unnamed: Q1.1 (D), R13.2
unnamed: Q1.2 (G), R11.2
unnamed: Q3.1 (G), R6.2
unnamed: FL1.1, U2.11 (RF_IN)
unnamed: C15.1, R15.2, U6.12 (RF)
RE: U5.2 (~RE), U6.30 (PB5)
RESET_N: U2.9 (~RESET), U6.32 (PB3/ADC1)
RST: C21.1, R14.2, U6.22 (RST)
RX: U6.1 (UART2_RX/PA3), U7.3 (TX1)
RX_5v: U4.10 (RXD), U7.6 (TX2)
RX_RS485: U5.1 (RO), U6.5 (UART1_RX/PB7)
STATUS_LED: R11.1, U6.20 (PA9)
TX: U6.2 (UART2_TX/PA2), U7.2 (RX1)
TX_5v: U4.7 (TXD), U7.7 (RX2)
TX_RS485: U5.4 (DI), U6.4 (UART1_TX/PB6)
USBDM: C2.1, R1.1, U4.1 (USBDM)
USBDP: C3.1, R2.1, U4.12 (USBDP)
VDD2: C11.1, C12.1, C23.1, FB1.1, U4.4 (VCC), U7.5 (VDD2)
V_BCKP: C5.1, C7.1, C13.1, C14.1, C16.1, C17.1, C18.1, C24.1, D1.2 (A), D3.1 (A1), Q3.2 (S), R10.1, R12.1, R14.1, U2.6 (V_BCKP), U3.5 (OUT), U5.8 (VCC), U6.24 (VCC), U7.1 (VDD1)

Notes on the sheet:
RS-485 - UART
RAK 3172 module & peripherals
USBC - UART
LDO 5v->3.3v

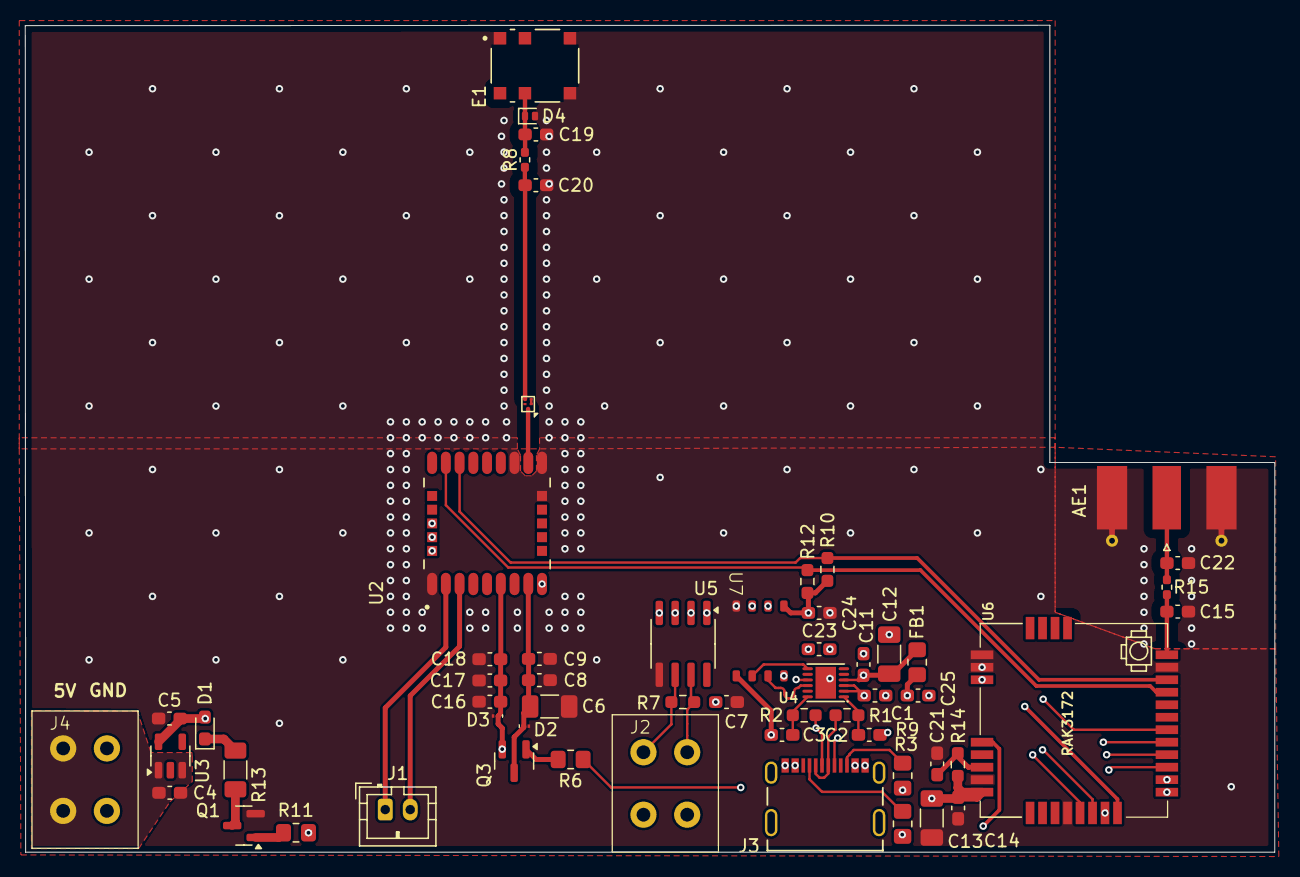
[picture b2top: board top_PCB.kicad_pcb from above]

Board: 4 copper layers, 100.0 x 66.2 mm, 57 parts (0 on the bottom side), 44 nets.

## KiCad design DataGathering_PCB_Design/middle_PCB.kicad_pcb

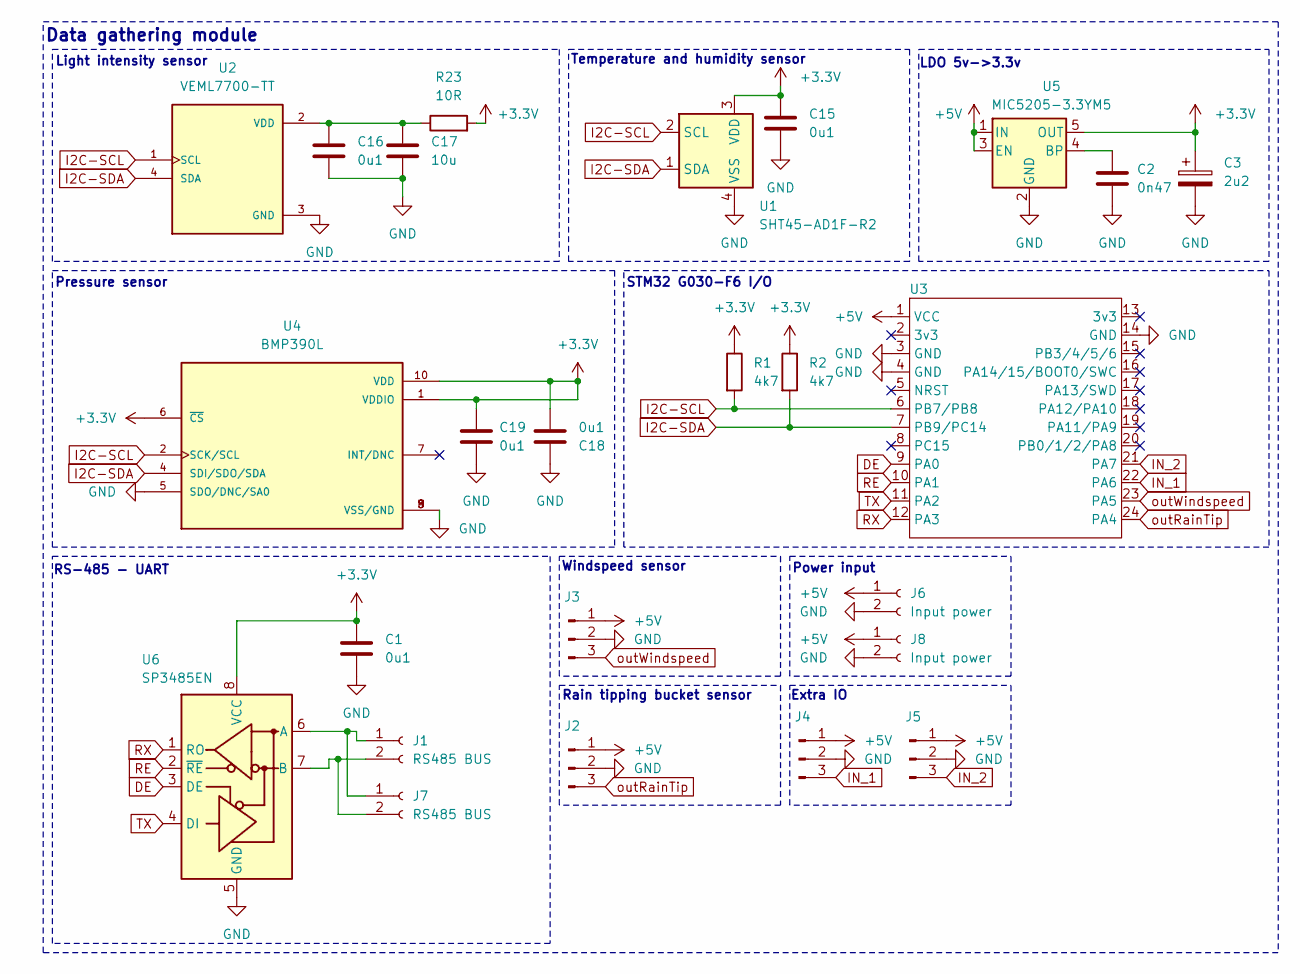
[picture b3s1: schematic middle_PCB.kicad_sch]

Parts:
C1, C15, C16, C18, C19: 0u1; C_0603_1608Metric_Pad1.08x0.95mm_HandSolder
C2: 0n47; C_0603_1608Metric_Pad1.08x0.95mm_HandSolder
C3: 2u2; C_1206_3216Metric_Pad1.33x1.80mm_HandSolder
C17: 10u; C_1206_3216Metric_Pad1.33x1.80mm_HandSolder
J1, J7: RS485 BUS; SPTAF 1_2-3,5-IL
J2, J3, J4, J5: Conn_01x03_Pin; SPTAF 1 3-3,5-IL
J6, J8: Input power; SPTAF 1_2-3,5-IL
R1, R2: 4k7; R_0603_1608Metric_Pad0.98x0.95mm_HandSolder
R23: 10R; R_0603_1608Metric_Pad0.98x0.95mm_HandSolder
U1: SHT45-AD1F-R2; Sensirion_DFN-4_1.5x1.5mm_P0.8mm_SHT4x_NoCentralPad
U2: VEML7700-TT; XDCR_VEML7700-TT; PARTREV 1.6
U3: STM32G030
U4: BMP390L; XDCR_BMP390L; PARTREV 1.7
U5: MIC5205-3.3YM5; SOT-23-5
U6: SP3485EN; SOIC-8_3.9x4.9mm_P1.27mm

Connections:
+3.3V: C1.1, C3.1, C15.1, C18.2, C19.1, R1.1, R2.1, R23.2, U1.3 (VDD), U4.1 (VDDIO), U4.6 (~CS), U4.10 (VDD), U5.5 (OUT), U6.8 (VCC)
+5V: J2.1, J3.1, J4.1, J5.1, J6.1, J8.1, U3.1 (VCC), U5.1 (IN), U5.3 (EN)
DE: U3.9 (PA0), U6.3 (DE)
GND: C1.2, C2.2, C3.2, C15.2, C16.2, C17.2, C18.1, C19.2, J2.2, J3.2, J4.2, J5.2, J6.2, J8.2, U1.4 (VSS), U2.3 (GND), U3.3 (GND), U3.4 (GND), U3.14 (GND), U4.3 (VSS/GND), U4.5 (SDO/DNC/SA0), U4.8 (VSS/GND), U4.9 (VSS/GND), U5.2 (GND), U6.5 (GND)
I2C-SCL: R1.2, U1.2 (SCL), U2.1 (SCL), U3.6 (PB7/PB8), U4.2 (SCK/SCL)
I2C-SDA: R2.2, U1.1 (SDA), U2.4 (SDA), U3.7 (PB9/PC14), U4.4 (SDI/SDO/SDA)
IN_1: J4.3, U3.22 (PA6)
IN_2: J5.3, U3.21 (PA7)
unnamed: J1.1, J7.1, U6.6 (A)
unnamed: J1.2, J7.2, U6.7 (B)
unnamed: C16.1, C17.1, R23.1, U2.2 (VDD)
unnamed: C2.1, U5.4 (BP)
RE: U3.10 (PA1), U6.2 (~RE)
RX: U3.12 (PA3), U6.1 (RO)
TX: U3.11 (PA2), U6.4 (DI)
outRainTip: J2.3, U3.24 (PA4)
outWindspeed: J3.3, U3.23 (PA5)

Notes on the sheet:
Data gathering module
RS-485 - UART
Windspeed sensor
Power input
Extra IO
Pressure sensor
LDO 5v->3.3v
STM32 G030-F6 I/O
Light intensity sensor
Temperature and humidity sensor
Rain tipping bucket sensor
